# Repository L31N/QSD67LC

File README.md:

View this project on [CADLAB.io](https://cadlab.io/project/1322). 

# QSD67LC
Quickshifter for Triumph Daytona 675 Bj. 06-08

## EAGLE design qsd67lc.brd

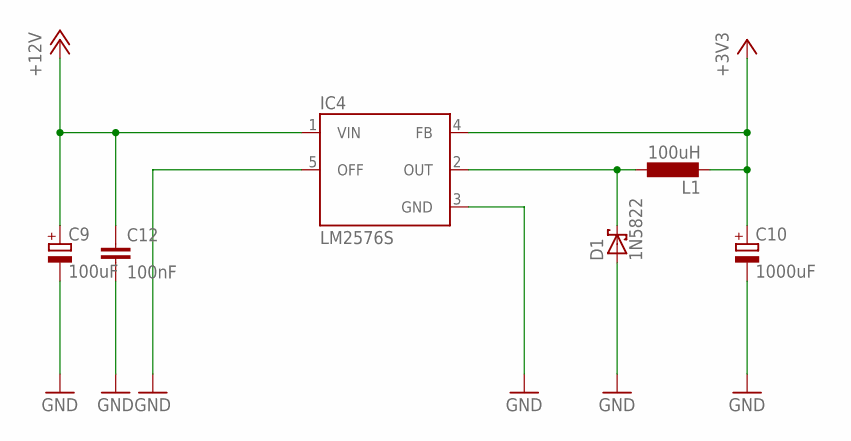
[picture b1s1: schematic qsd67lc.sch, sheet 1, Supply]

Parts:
C9: 100uF; E5-13
C10: 1000uF; E5-10,5
C12: 100nF; C0805
D1: 1N5822; DO201T15
IC4: LM2576S; TO263-5
L1: 100uH; 2200-15.24

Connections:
+3V3: C10.+, IC4.4 (FB), L1.2; also elsewhere on the board
+12V: C9.+, C12.1, IC4.1 (VIN); also elsewhere on the board
GND: C9.-, C10.-, C12.2, D1.A, IC4.3 (GND), IC4.5 (OFF); also elsewhere on the board
unnamed: D1.C, IC4.2 (OUT), L1.1

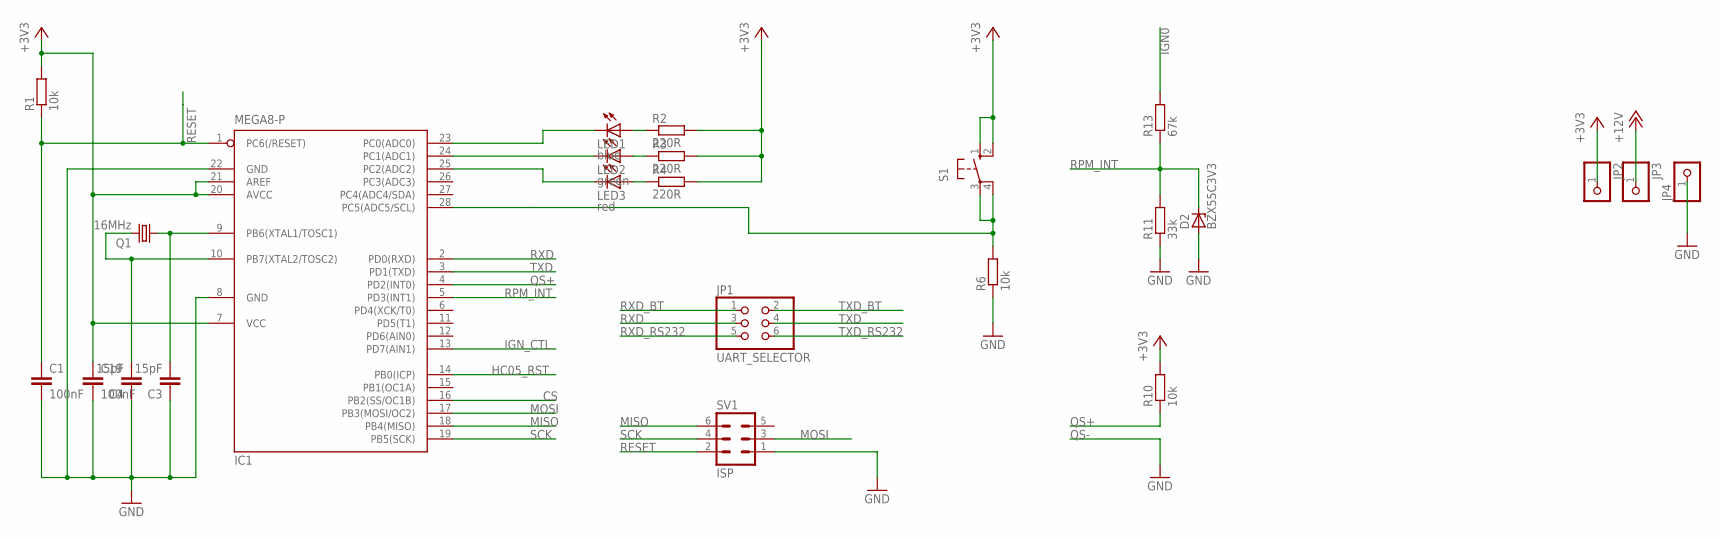
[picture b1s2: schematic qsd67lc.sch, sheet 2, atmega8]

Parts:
C1, C19: 100nF; C0805
C3, C4: 15pF; C0805
D2: BZX55C3V3; DO35Z10
IC1: MEGA8-P; DIL28-3
JP1: UART_SELECTOR; 2X03
JP2, JP3, JP4: PINHD-1X1; 1X01
LED1: blue; CHIP-LED0805
LED2: green; CHIP-LED0805
LED3: red; CHIP-LED0805
Q1: 16MHz; HC18U-V
R1, R6, R10: 10k; R0805
R2, R3, R4: 220R; R0805
R11: 33k; R0805
R13: 67k; R0805
S1: 10-XX; B3F-10XX
SV1: ISP; ML6

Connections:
+3V3: C19.1, IC1.7 (VCC), IC1.20 (AVCC), IC1.21 (AREF), JP2.1, R1.2, R2.2, R3.2, R4.2, R10.2, S1.1 (S), S1.2 (S1); also elsewhere on the board
+12V: JP3.1; also elsewhere on the board
CS: IC1.16 (PB2(SS/OC1B))
GND: C1.2, C3.1, C4.1, C19.2, D2.A, IC1.8 (GND), IC1.22 (GND), JP4.1, R6.1, R11.1, SV1.1; also elsewhere on the board
HC05_RST: IC1.14 (PB0(ICP)); also elsewhere on the board
IGN0: R13.2; also elsewhere on the board
IGN_CTL: IC1.13 (PD7(AIN1)); also elsewhere on the board
MISO: IC1.18 (PB4(MISO)), SV1.6
MOSI: IC1.17 (PB3(MOSI/OC2)), SV1.3
unnamed: IC1.24 (PC1(ADC1)), LED2.C
unnamed: C3.2, IC1.9 (PB6(XTAL1/TOSC1)), Q1.1
unnamed: C4.2, IC1.10 (PB7(XTAL2/TOSC2)), Q1.2
unnamed: LED2.A, R3.1
unnamed: LED1.A, R2.1
unnamed: LED3.A, R4.1
unnamed: IC1.23 (PC0(ADC0)), LED1.C
unnamed: IC1.25 (PC2(ADC2)), LED3.C
unnamed: IC1.28 (PC5(ADC5/SCL)), R6.2, S1.3, S1.4 (P1)
QS+: IC1.4 (PD2(INT0)), R10.1; also elsewhere on the board
RESET: C1.1, IC1.1 (PC6(/RESET)), R1.1, SV1.2
RPM_INT: D2.C, IC1.5 (PD3(INT1)), R11.2, R13.1
RXD: IC1.2 (PD0(RXD)), JP1.3
RXD_BT: JP1.1; also elsewhere on the board
RXD_RS232: JP1.5; also elsewhere on the board
SCK: IC1.19 (PB5(SCK)), SV1.4
TXD: IC1.3 (PD1(TXD)), JP1.4
TXD_BT: JP1.2; also elsewhere on the board
TXD_RS232: JP1.6; also elsewhere on the board

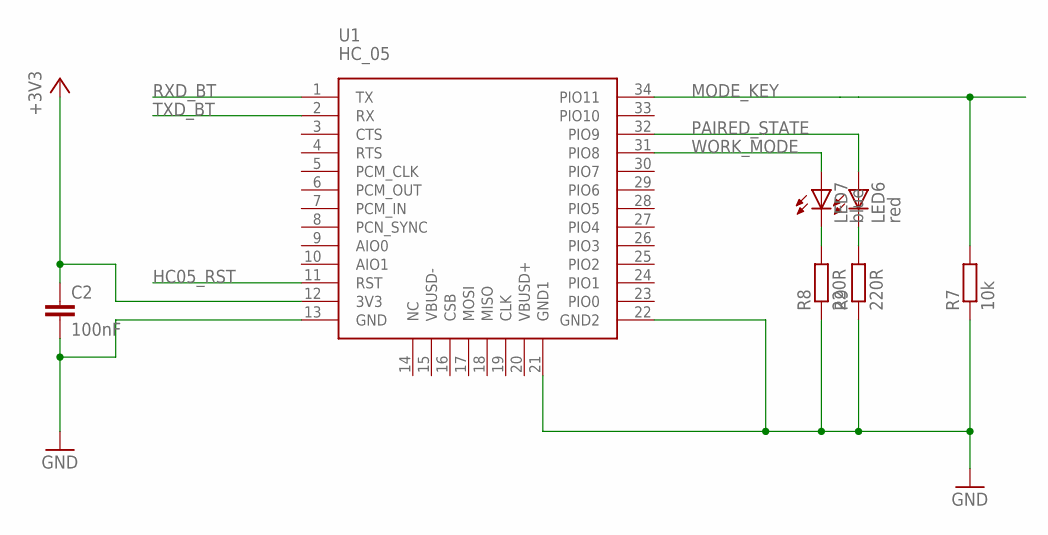
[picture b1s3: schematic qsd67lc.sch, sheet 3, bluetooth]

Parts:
C2: 100nF; C0805
LED6: red; CHIP-LED0805
LED7: blue; CHIP-LED0805
R7: 10k; R0805
R8, R9: 220R; R0805
U1: HC_05; BLUETOOTH_SMD

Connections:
+3V3: C2.1, U1.12 (3V3); also elsewhere on the board
GND: C2.2, R7.1, R8.1, R9.1, U1.13 (GND), U1.21 (GND1), U1.22 (GND2); also elsewhere on the board
HC05_RST: U1.11 (RST); also elsewhere on the board
MODE_KEY: R7.2, U1.34 (PIO11)
unnamed: LED7.C, R8.2
unnamed: LED6.C, R9.2
PAIRED_STATE: LED6.A, U1.32 (PIO9)
RXD_BT: U1.1 (TX); also elsewhere on the board
TXD_BT: U1.2 (RX); also elsewhere on the board
WORK_MODE: LED7.A, U1.31 (PIO8)

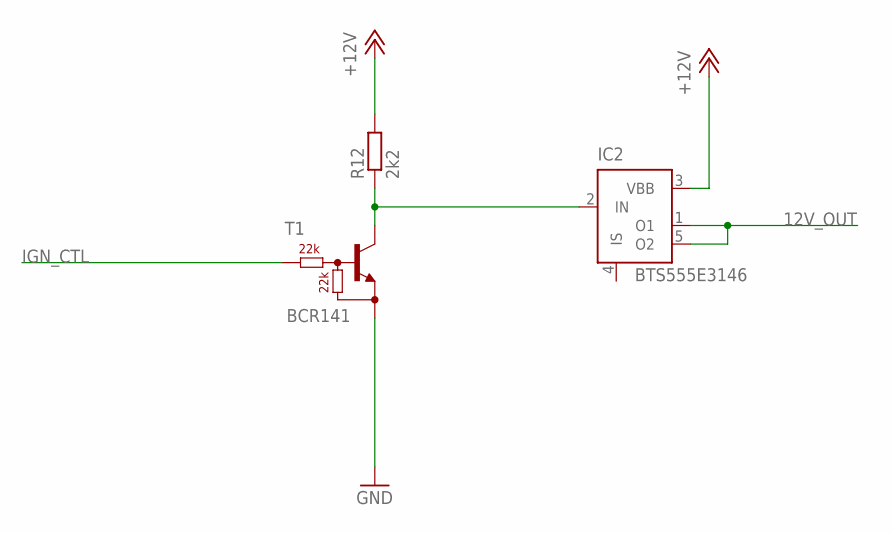
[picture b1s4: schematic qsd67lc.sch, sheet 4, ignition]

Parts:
IC2: BTS555E3146; TO220-52
R12: 2k2; R0805
T1: BCR141; SOT23-R_INFINEON

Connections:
12V_OUT: IC2.1 (O1), IC2.5 (O2); also elsewhere on the board
+12V: IC2.3 (VBB), R12.2; also elsewhere on the board
GND: T1.2 (E); also elsewhere on the board
IGN_CTL: T1.1 (B); also elsewhere on the board
unnamed: IC2.2 (IN), R12.1, T1.3 (C)

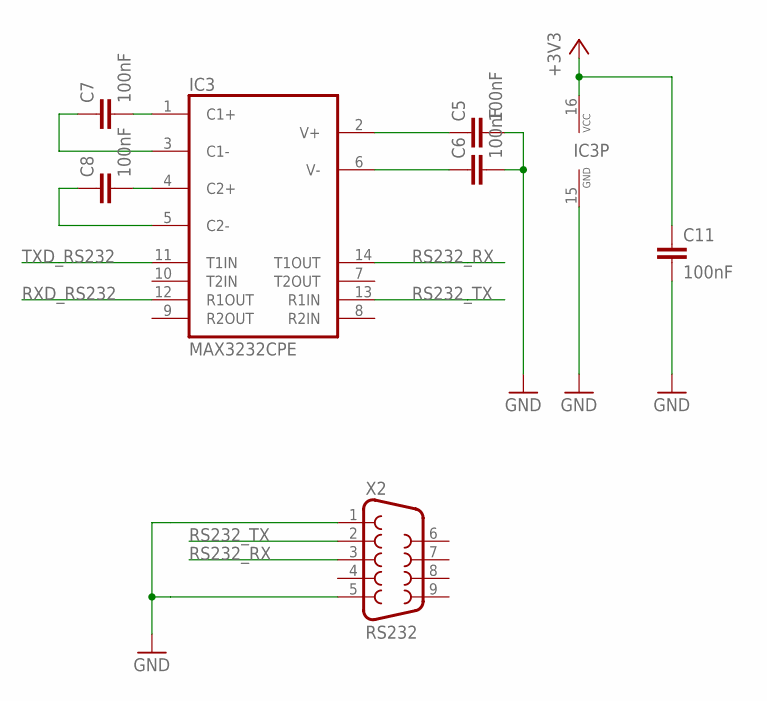
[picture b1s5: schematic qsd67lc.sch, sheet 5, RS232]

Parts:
C5, C6, C7, C8, C11: 100nF; C0805
IC3: MAX3232CPE; DIL16
X2: RS232; F09HP

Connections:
+3V3: C11.1, IC3.16 (VCC); also elsewhere on the board
GND: C5.2, C6.2, C11.2, IC3.15 (GND), X2.1, X2.5; also elsewhere on the board
unnamed: C5.1, IC3.2 (V+)
unnamed: C6.1, IC3.6 (V-)
unnamed: C7.2, IC3.1 (C1+)
unnamed: C8.2, IC3.4 (C2+)
unnamed: C8.1, IC3.5 (C2-)
unnamed: C7.1, IC3.3 (C1-)
RS232_RX: IC3.14 (T1OUT), X2.3
RS232_TX: IC3.13 (R1IN), X2.2
RXD_RS232: IC3.12 (R1OUT); also elsewhere on the board
TXD_RS232: IC3.11 (T1IN); also elsewhere on the board

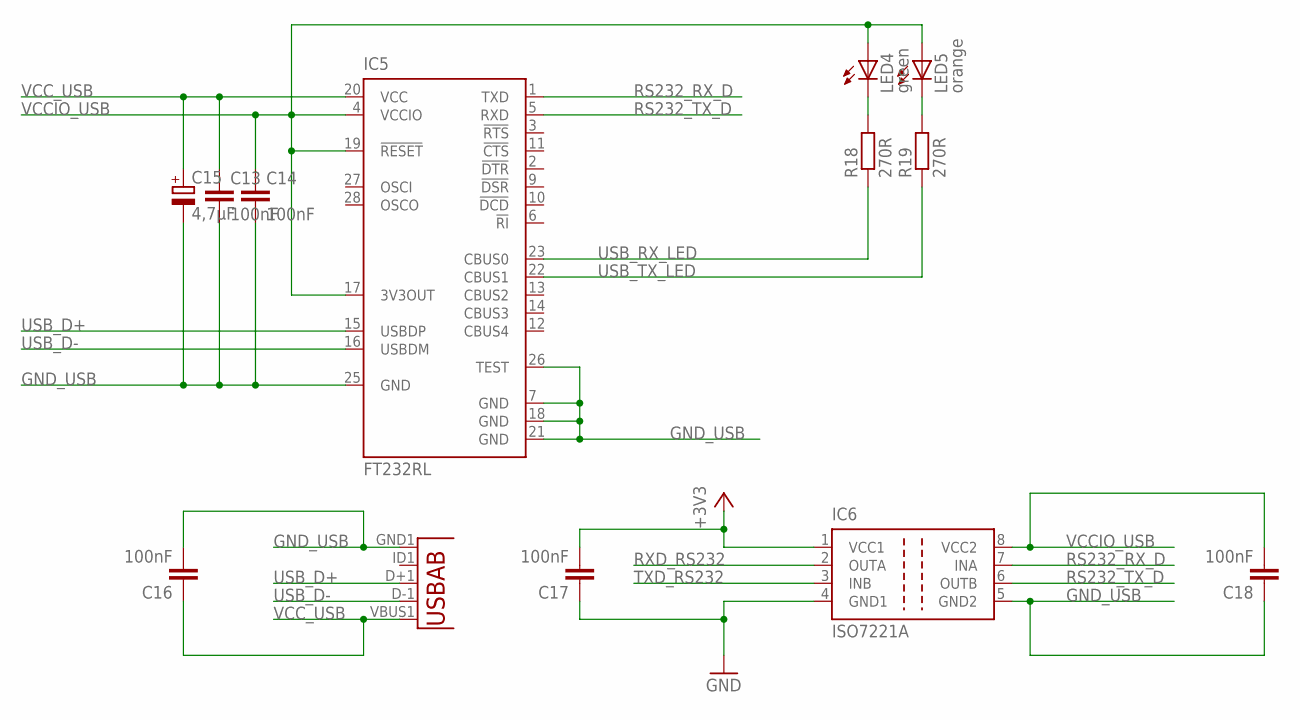
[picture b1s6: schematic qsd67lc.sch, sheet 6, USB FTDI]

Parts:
C13, C14, C16, C17, C18: 100nF; C0805
C15: 4,7µF; E2,5-5
IC5: FT232RL; SSOP28
IC6: ISO7221A; SO-08
LED4: green; SML0805
LED5: orange; SML0805
R18, R19: 270R; R0805
U2: USB""; USB-MICRO-SMD

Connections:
+3V3: C17.2, IC6.1 (VCC1); also elsewhere on the board
GND: C17.1, IC6.4 (GND1); also elsewhere on the board
GND_USB: C13.2, C14.2, C15.-, C16.2, C18.1, IC5.7 (GND), IC5.18 (GND), IC5.21 (GND), IC5.25 (GND), IC5.26 (TEST), IC6.5 (GND2), U2.GND1 (GND)
unnamed: LED4.C, R18.2
unnamed: LED5.C, R19.2
RS232_RX_D: IC5.1 (TXD), IC6.7 (INA)
RS232_TX_D: IC5.5 (RXD), IC6.6 (OUTB)
RXD_RS232: IC6.2 (OUTA); also elsewhere on the board
TXD_RS232: IC6.3 (INB); also elsewhere on the board
USB_D+: IC5.15 (USBDP), U2.D+1 (D+)
USB_D-: IC5.16 (USBDM), U2.D-1 (D-)
USB_RX_LED: IC5.23 (CBUS0), R18.1
USB_TX_LED: IC5.22 (CBUS1), R19.1
VCCIO_USB: C14.1, C18.2, IC5.4 (VCCIO), IC5.17 (3V3OUT), IC5.19 (!RESET), IC6.8 (VCC2), LED4.A, LED5.A
VCC_USB: C13.1, C15.+, C16.1, IC5.20 (VCC), U2.VBUS1 (VBUS)

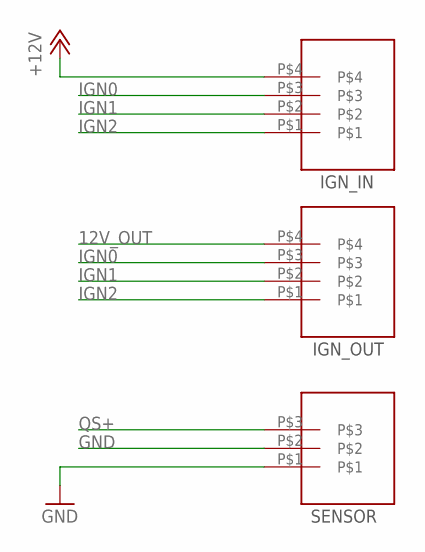
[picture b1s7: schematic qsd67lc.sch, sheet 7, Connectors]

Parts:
CON1, CON2: RIA-AKL-230-04; CON-RIA-P4
CON3: RIA-AKL-230-03; CON-RIA-P3

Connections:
12V_OUT: CON2.P$4; also elsewhere on the board
+12V: CON1.P$4; also elsewhere on the board
GND: CON3.P$1, CON3.P$2; also elsewhere on the board
IGN0: CON1.P$3, CON2.P$3; also elsewhere on the board
IGN1: CON1.P$2, CON2.P$2
IGN2: CON1.P$1, CON2.P$1
QS+: CON3.P$3; also elsewhere on the board

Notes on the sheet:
IGN_IN
IGN_OUT
SENSOR

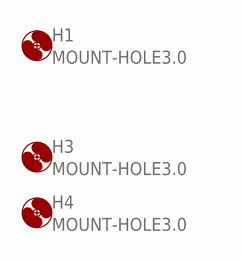
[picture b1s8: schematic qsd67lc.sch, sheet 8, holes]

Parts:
H1, H3, H4: MOUNT-HOLE3.0; 3,0

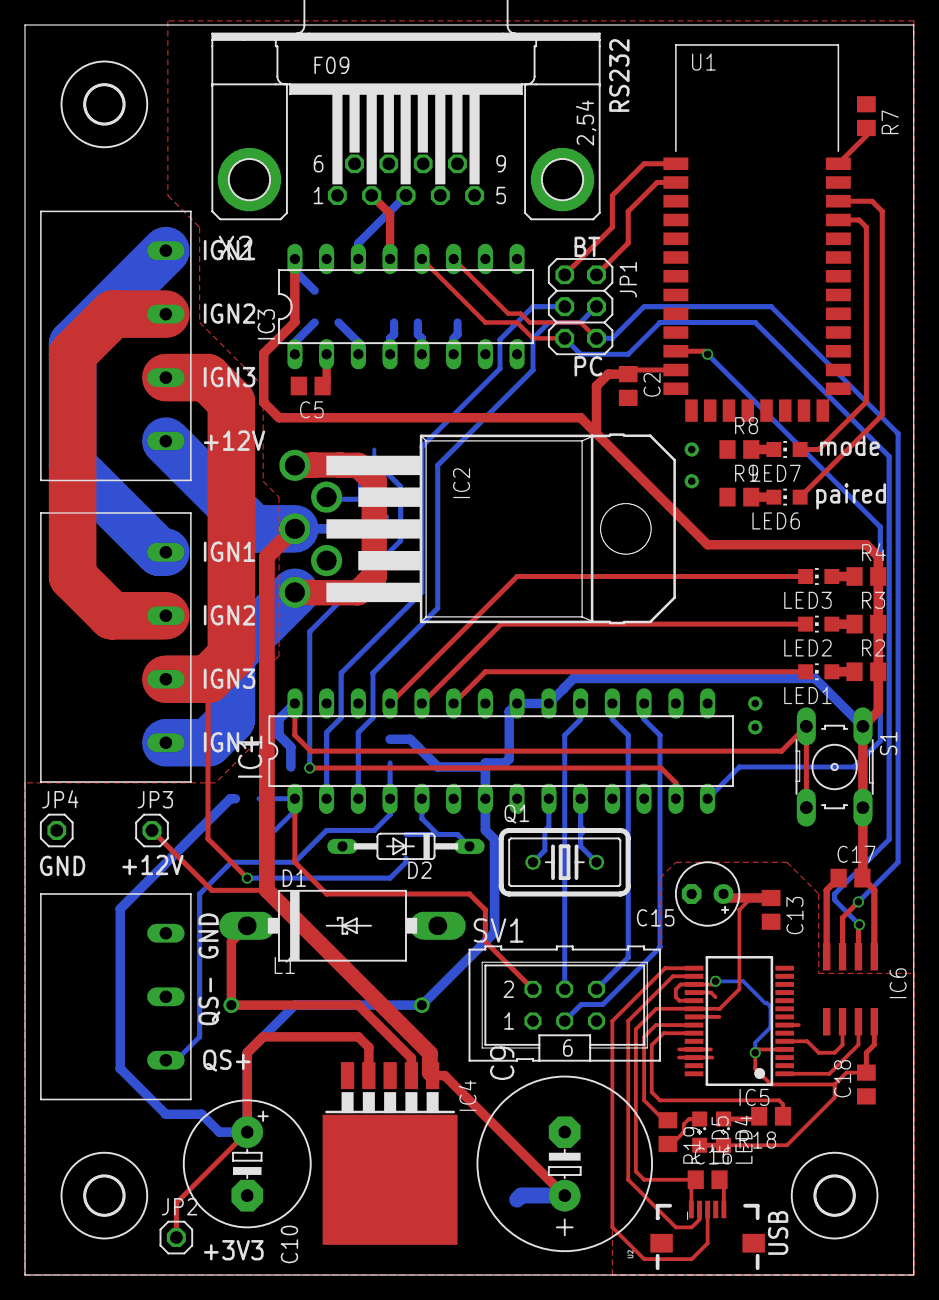
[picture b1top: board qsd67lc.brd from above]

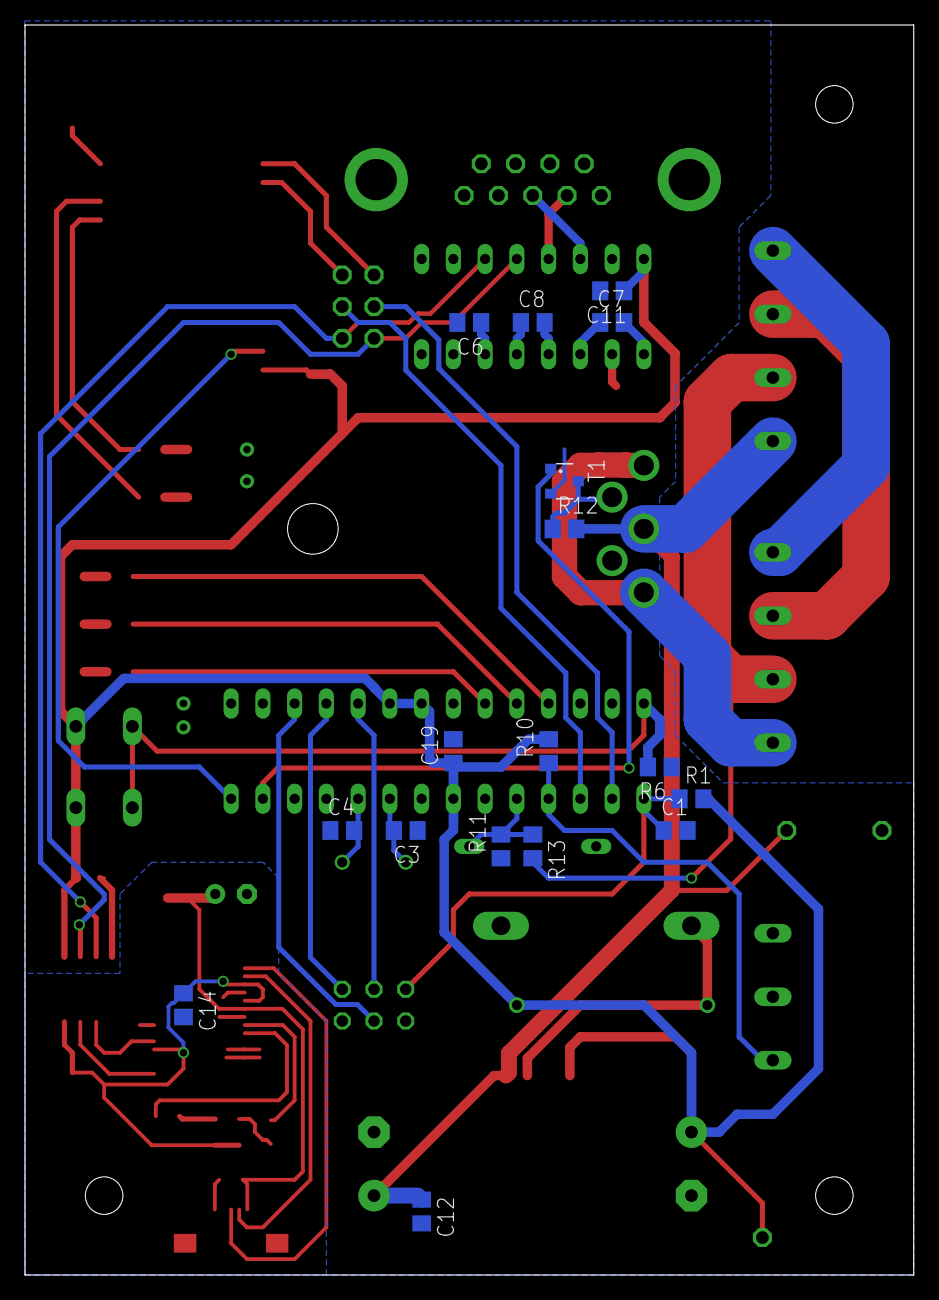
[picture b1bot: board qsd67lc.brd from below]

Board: 2 copper layers, 71.1 x 100.0 mm, 66 parts (17 on the bottom side), 56 nets.

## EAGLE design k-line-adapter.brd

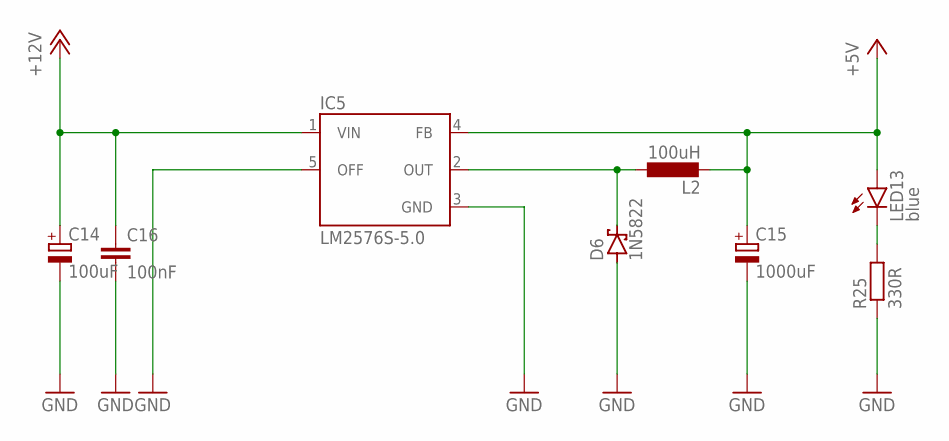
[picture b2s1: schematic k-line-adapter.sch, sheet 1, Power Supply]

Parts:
C14: 100uF; E5-10,5
C15: 1000uF; E5-10,5
C16: 100nF; C0805
D6: 1N5822; DO201T15
IC5: LM2576S-5.0; TO263-5
L2: 100uH; 09HCP
LED13: blue; CHIP-LED0805
R25: 330R; R0805

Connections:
+5V: C15.+, IC5.4 (FB), L2.P$2 (2), LED13.A; also elsewhere on the board
+12V: C14.+, C16.1, IC5.1 (VIN); also elsewhere on the board
GND: C14.-, C15.-, C16.2, D6.A, IC5.3 (GND), IC5.5 (OFF), R25.1; also elsewhere on the board
unnamed: D6.C, IC5.2 (OUT), L2.P$1 (1)
unnamed: LED13.C, R25.2

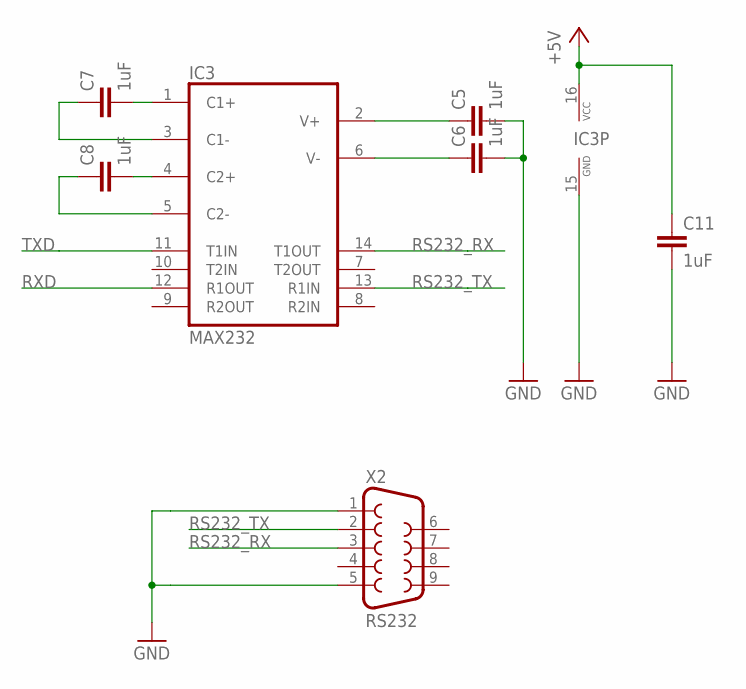
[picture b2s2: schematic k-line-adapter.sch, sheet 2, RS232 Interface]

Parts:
C5, C6, C7, C8, C11: 1uF; C0805
IC3: MAX232; DIL16
X2: RS232; F09HP

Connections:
+5V: C11.1, IC3.16 (VCC); also elsewhere on the board
GND: C5.2, C6.2, C11.2, IC3.15 (GND), X2.1, X2.5; also elsewhere on the board
unnamed: C5.1, IC3.2 (V+)
unnamed: C6.1, IC3.6 (V-)
unnamed: C7.2, IC3.1 (C1+)
unnamed: C8.2, IC3.4 (C2+)
unnamed: C8.1, IC3.5 (C2-)
unnamed: C7.1, IC3.3 (C1-)
RS232_RX: IC3.14 (T1OUT), X2.3
RS232_TX: IC3.13 (R1IN), X2.2
RXD: IC3.12 (R1OUT); also elsewhere on the board
TXD: IC3.11 (T1IN); also elsewhere on the board

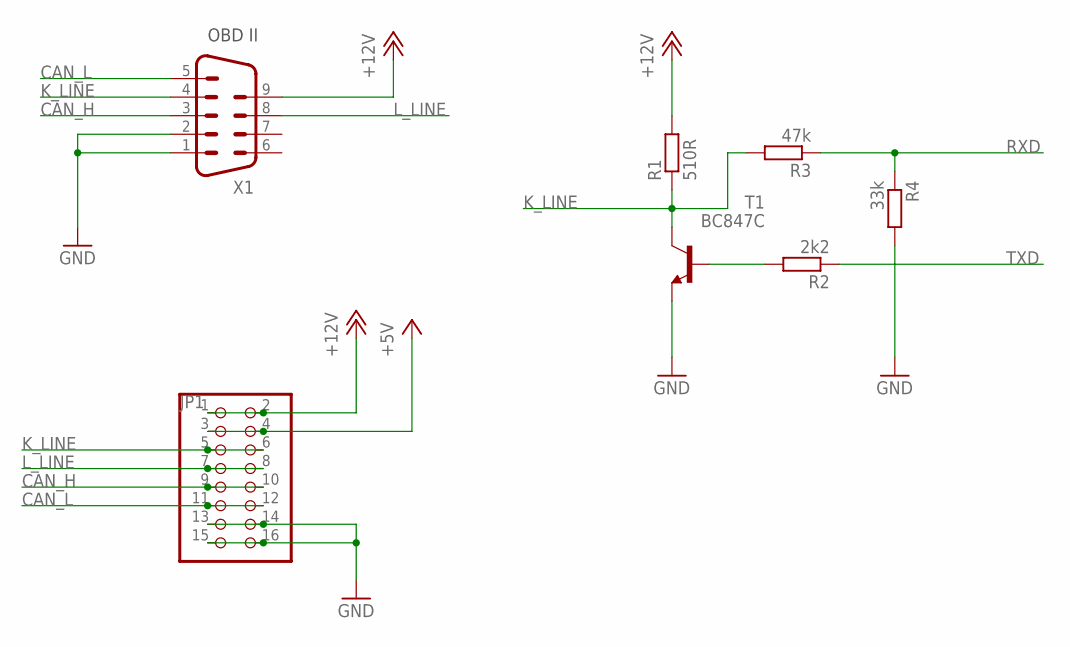
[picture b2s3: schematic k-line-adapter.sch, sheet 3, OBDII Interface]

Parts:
JP1: PINHD-2X8; 2X08
R1: 510R; R0805
R2: 2k2; R0805
R3: 47k; R0805
R4: 33k; R0805
T1: BC847C; SOT23-BEC
X1: M09HP

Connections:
+5V: JP1.3, JP1.4; also elsewhere on the board
+12V: JP1.1, JP1.2, R1.2, X1.9; also elsewhere on the board
CAN_H: JP1.9, JP1.10, X1.3
CAN_L: JP1.11, JP1.12, X1.5
GND: JP1.13, JP1.14, JP1.15, JP1.16, R4.2, T1.E, X1.1, X1.2; also elsewhere on the board
K_LINE: JP1.5, JP1.6, R1.1, R3.2, T1.C, X1.4
L_LINE: JP1.7, JP1.8, X1.8
unnamed: R2.2, T1.B
RXD: R3.1, R4.1; also elsewhere on the board
TXD: R2.1; also elsewhere on the board

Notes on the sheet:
OBD II

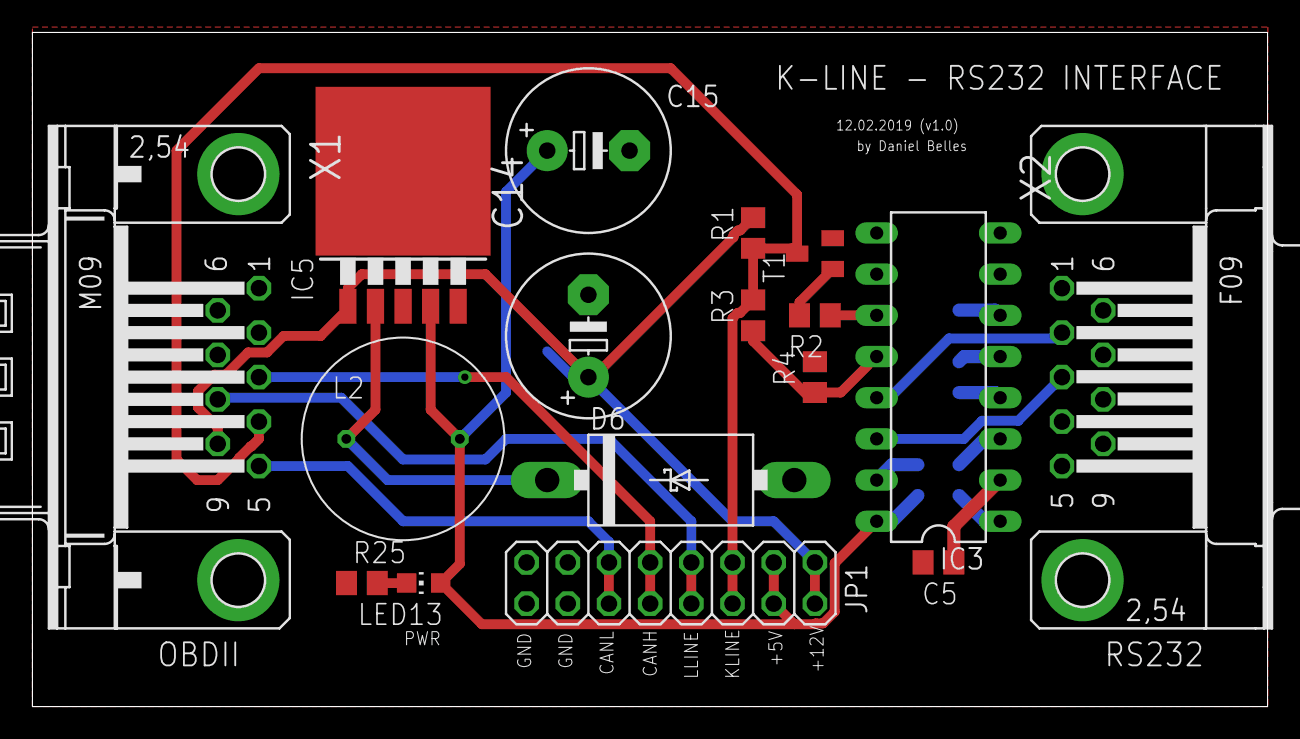
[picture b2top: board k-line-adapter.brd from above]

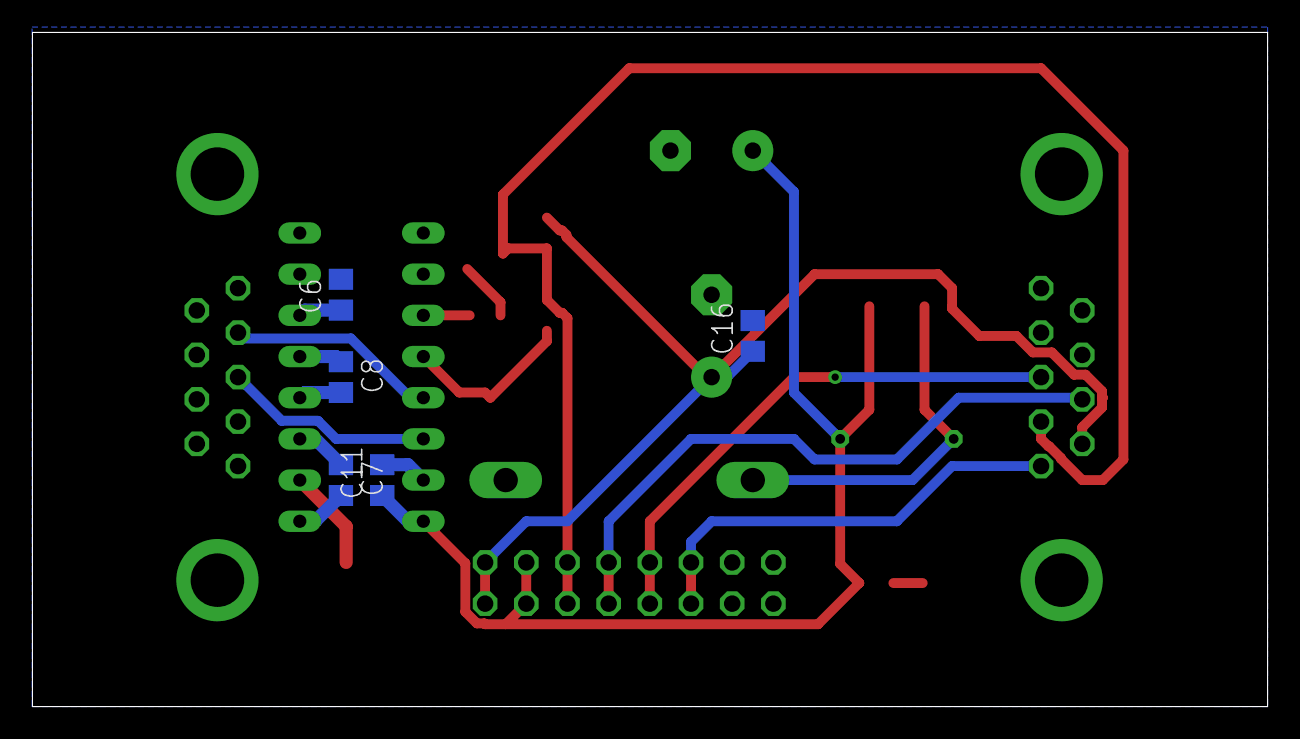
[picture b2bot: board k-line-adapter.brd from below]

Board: 2 copper layers, 76.2 x 41.6 mm, 22 parts (5 on the bottom side), 20 nets.

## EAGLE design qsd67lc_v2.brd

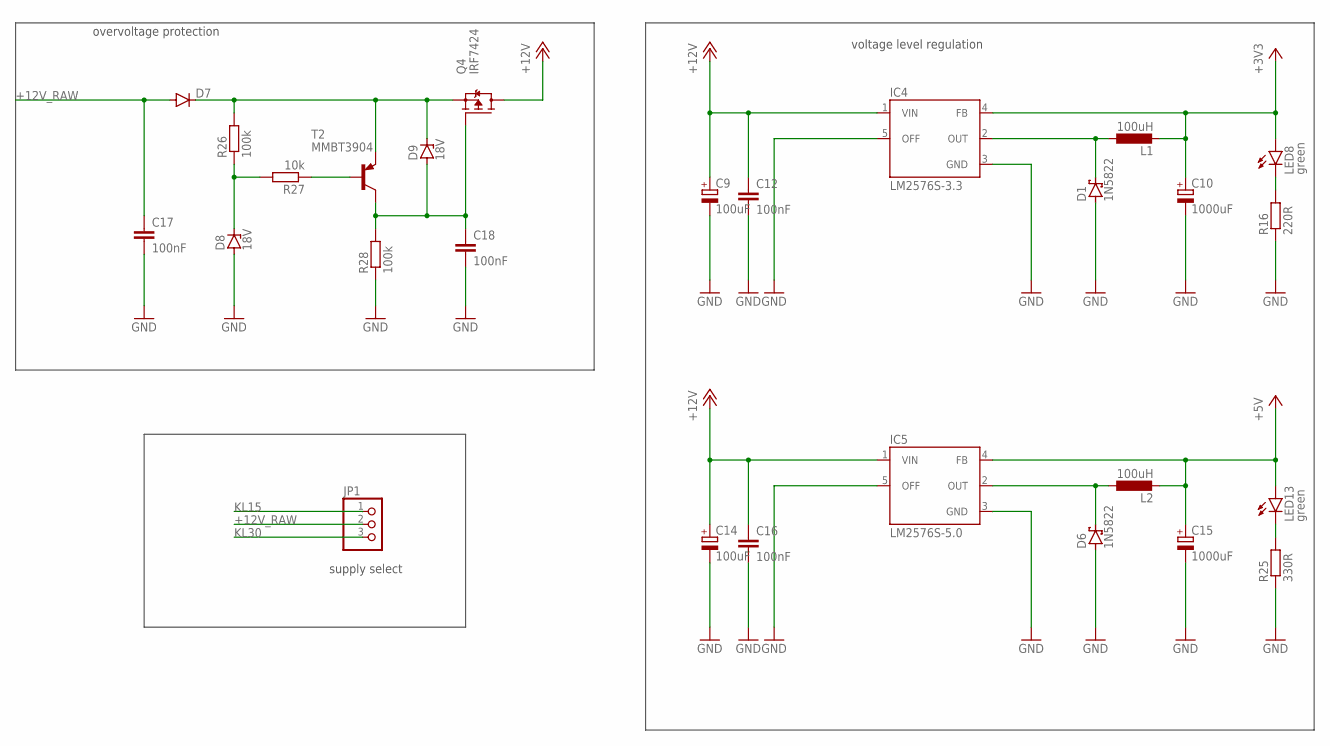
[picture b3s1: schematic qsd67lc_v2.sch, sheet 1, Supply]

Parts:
C9, C14: 100uF; E5-10,5
C10, C15: 1000uF; E5-10,5
C12, C16, C17, C18: 100nF; C0805
D1, D6: 1N5822; DO201T15
D7: DIODE-SOD123; SOD123
D8, D9: 18V; SOD80C
IC4: LM2576S-3.3; TO263-5
IC5: LM2576S-5.0; TO263-5
JP1: PINHD-1X3; 1X03
L1, L2: 100uH; 09HCP
LED8, LED13: green; CHIP-LED0805
Q4: IRF7424; SO-8
R16: 220R; R0805
R25: 330R; R0805
R26, R28: 100k; R0805
R27: 10k; R0805
T2: MMBT3904; SOT23-BEC

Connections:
+3V3: C10.+, IC4.4 (FB), L1.P$2 (2), LED8.A; also elsewhere on the board
+5V: C15.+, IC5.4 (FB), L2.P$2 (2), LED13.A; also elsewhere on the board
+12V: C9.+, C12.1, C14.+, C16.1, IC4.1 (VIN), IC5.1 (VIN), Q4.5 (D), Q4.6 (D), Q4.7 (D), Q4.8 (D); also elsewhere on the board
+12V_RAW: C17.1, D7.A, JP1.2
GND: C9.-, C10.-, C12.2, C14.-, C15.-, C16.2, C17.2, C18.2, D1.A, D6.A, D8.A, IC4.3 (GND), IC4.5 (OFF), IC5.3 (GND), IC5.5 (OFF), R16.1, R25.1, R28.1; also elsewhere on the board
KL15: JP1.1; also elsewhere on the board
KL30: JP1.3; also elsewhere on the board
unnamed: LED8.C, R16.2
unnamed: D7.C, D9.C, Q4.1 (S), Q4.2 (S), Q4.3 (S), R26.2, T2.E
unnamed: D1.C, IC4.2 (OUT), L1.P$1 (1)
unnamed: D6.C, IC5.2 (OUT), L2.P$1 (1)
unnamed: LED13.C, R25.2
unnamed: D8.C, R26.1, R27.2
unnamed: R27.1, T2.B
unnamed: C18.1, D9.A, Q4.4 (G), R28.2, T2.C

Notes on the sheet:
supply select
overvoltage protection
voltage level regulation

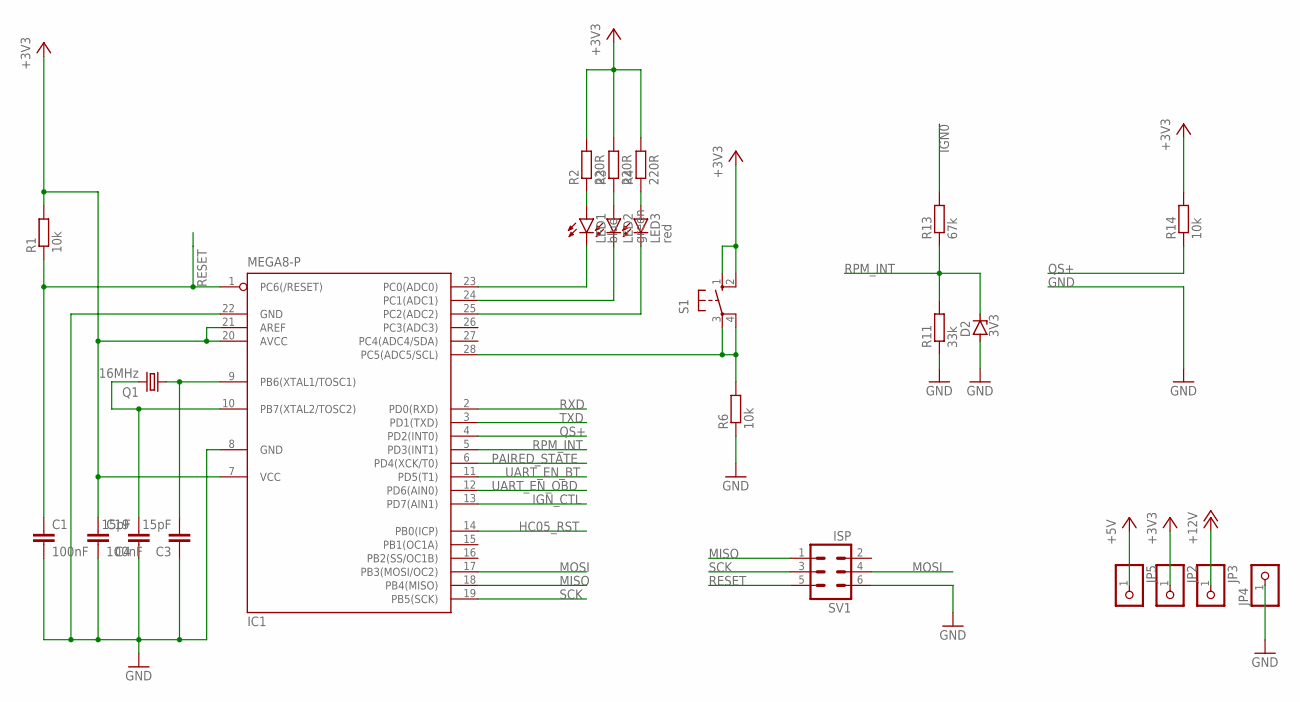
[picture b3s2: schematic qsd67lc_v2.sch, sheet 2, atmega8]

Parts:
C1, C19: 100nF; C0805
C3, C4: 15pF; C0805
D2: 3V3; SOD80C
IC1: MEGA8-P; DIL28-3
JP2, JP3, JP4, JP5: PINHD-1X1; 1X01
LED1: blue; CHIP-LED0805
LED2: green; CHIP-LED0805
LED3: red; CHIP-LED0805
Q1: 16MHz; HC49U-V
R1, R6, R14: 10k; R0805
R2, R3, R4: 220R; R0805
R11: 33k; R0805
R13: 67k; R0805
S1: 10-XX; B3F-10XX
SV1: ISP; ML6

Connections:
+3V3: C19.1, IC1.7 (VCC), IC1.20 (AVCC), IC1.21 (AREF), JP2.1, R1.2, R2.2, R3.2, R4.2, R14.2, S1.1 (S), S1.2 (S1); also elsewhere on the board
+5V: JP5.1; also elsewhere on the board
+12V: JP3.1; also elsewhere on the board
GND: C1.2, C3.1, C4.1, C19.2, D2.A, IC1.8 (GND), IC1.22 (GND), JP4.1, R6.1, R11.1, SV1.6; also elsewhere on the board
HC05_RST: IC1.14 (PB0(ICP)); also elsewhere on the board
IGN0: R13.2; also elsewhere on the board
IGN_CTL: IC1.13 (PD7(AIN1)); also elsewhere on the board
MISO: IC1.18 (PB4(MISO)), SV1.1
MOSI: IC1.17 (PB3(MOSI/OC2)), SV1.4
unnamed: C3.2, IC1.9 (PB6(XTAL1/TOSC1)), Q1.1
unnamed: C4.2, IC1.10 (PB7(XTAL2/TOSC2)), Q1.2
unnamed: LED2.A, R3.1
unnamed: LED1.A, R2.1
unnamed: LED3.A, R4.1
unnamed: IC1.23 (PC0(ADC0)), LED1.C
unnamed: IC1.24 (PC1(ADC1)), LED2.C
unnamed: IC1.28 (PC5(ADC5/SCL)), R6.2, S1.3, S1.4 (P1)
unnamed: IC1.25 (PC2(ADC2)), LED3.C
PAIRED_STATE: IC1.6 (PD4(XCK/T0)); also elsewhere on the board
QS+: IC1.4 (PD2(INT0)), R14.1; also elsewhere on the board
RESET: C1.1, IC1.1 (PC6(/RESET)), R1.1, SV1.5
RPM_INT: D2.C, IC1.5 (PD3(INT1)), R11.2, R13.1
RXD: IC1.2 (PD0(RXD)); also elsewhere on the board
SCK: IC1.19 (PB5(SCK)), SV1.3
TXD: IC1.3 (PD1(TXD)); also elsewhere on the board
UART_EN_BT: IC1.11 (PD5(T1)); also elsewhere on the board
UART_EN_OBD: IC1.12 (PD6(AIN0)); also elsewhere on the board

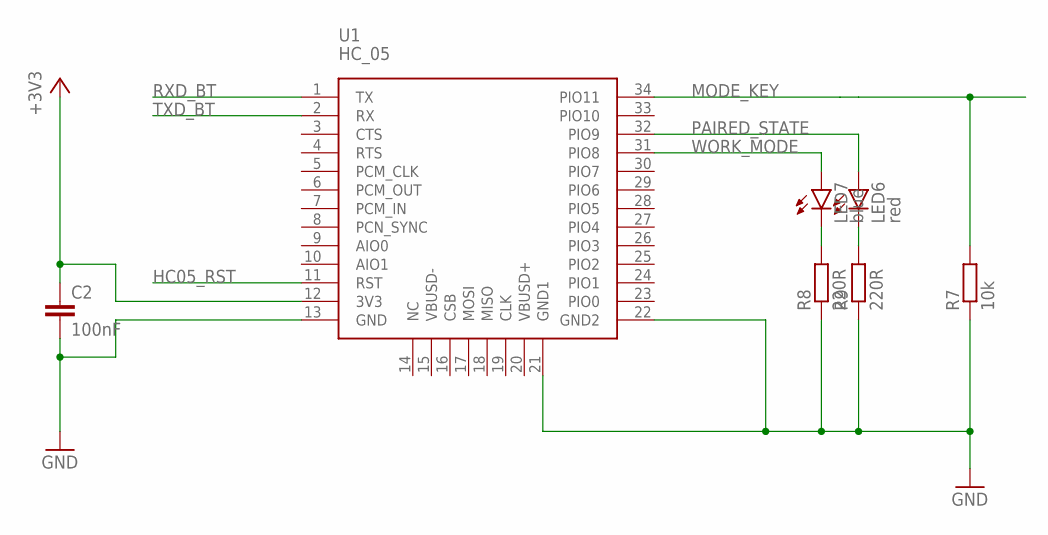
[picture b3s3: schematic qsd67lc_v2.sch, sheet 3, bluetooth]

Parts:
C2: 100nF; C0805
LED6: red; CHIP-LED0805
LED7: blue; CHIP-LED0805
R7: 10k; R0805
R8, R9: 220R; R0805
U1: HC_05; BLUETOOTH_SMD

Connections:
+3V3: C2.1, U1.12 (3V3); also elsewhere on the board
GND: C2.2, R7.1, R8.1, R9.1, U1.13 (GND), U1.21 (GND1), U1.22 (GND2); also elsewhere on the board
HC05_RST: U1.11 (RST); also elsewhere on the board
MODE_KEY: R7.2, U1.34 (PIO11)
unnamed: LED7.C, R8.2
unnamed: LED6.C, R9.2
PAIRED_STATE: LED6.A, U1.32 (PIO9); also elsewhere on the board
RXD_BT: U1.1 (TX); also elsewhere on the board
TXD_BT: U1.2 (RX); also elsewhere on the board
WORK_MODE: LED7.A, U1.31 (PIO8)

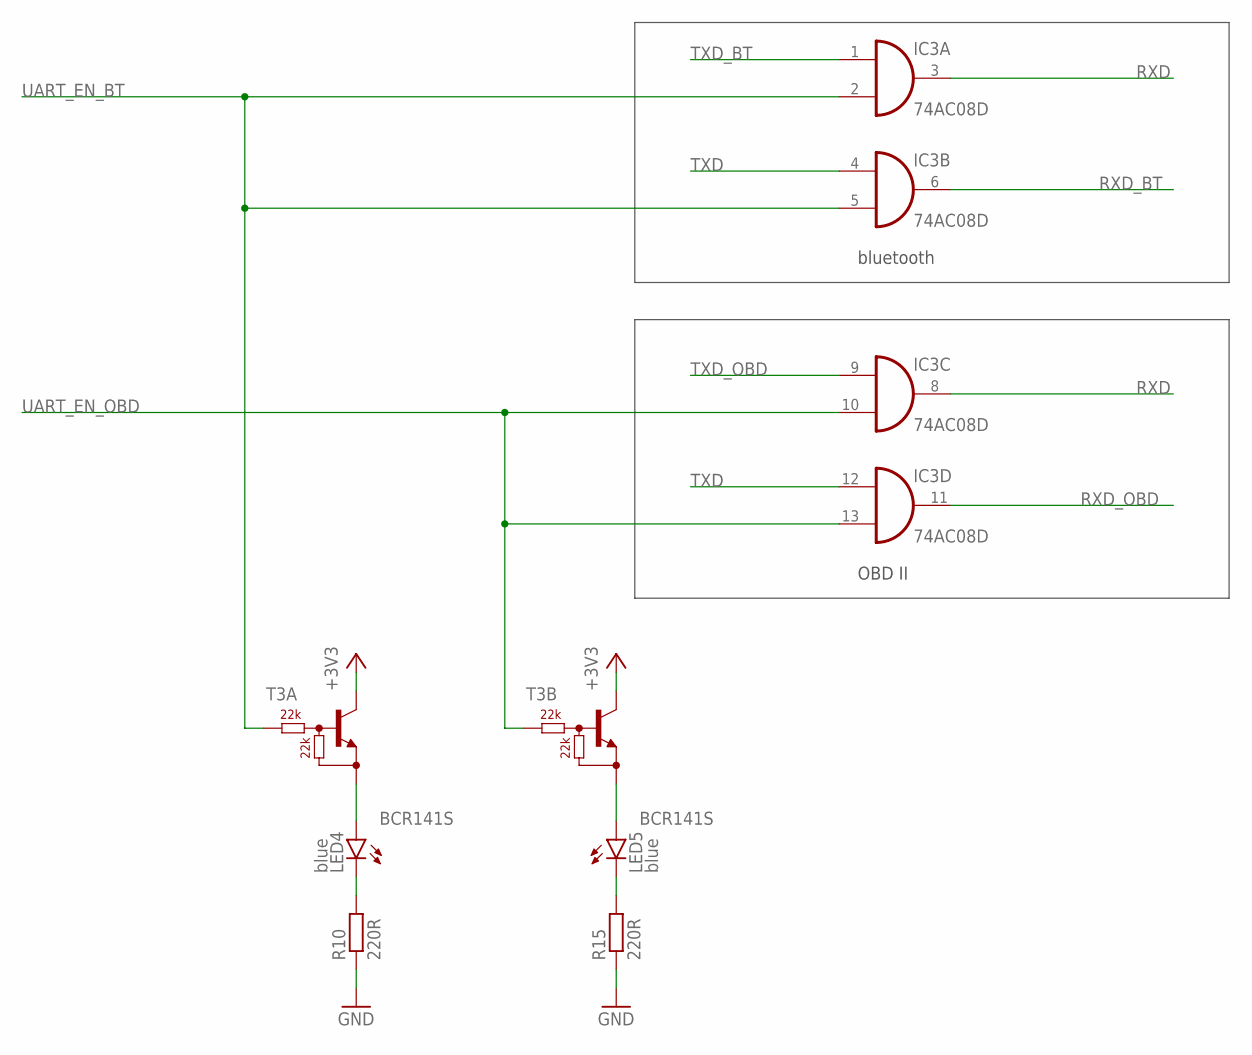
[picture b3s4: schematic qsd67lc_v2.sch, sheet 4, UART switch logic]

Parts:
IC3: 74AC08D; SO14
LED4, LED5: blue; CHIP-LED0805
R10, R15: 220R; M0805
T3: BCR141S; SOT363_INFINEON

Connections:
+3V3: T3.3 (C), T3.6 (C); also elsewhere on the board
GND: IC3.7 (GND), R10.1, R15.1; also elsewhere on the board
unnamed: LED4.C, R10.2
unnamed: LED5.C, R15.2
unnamed: LED4.A, T3.1 (E)
unnamed: LED5.A, T3.4 (E)
RXD: IC3.3 (O), IC3.8 (O); also elsewhere on the board
RXD_BT: IC3.6 (O); also elsewhere on the board
RXD_OBD: IC3.11 (O); also elsewhere on the board
TXD: IC3.4 (I0), IC3.12 (I0); also elsewhere on the board
TXD_BT: IC3.1 (I0); also elsewhere on the board
TXD_OBD: IC3.9 (I0); also elsewhere on the board
UART_EN_BT: IC3.2 (I1), IC3.5 (I1), T3.2 (B); also elsewhere on the board
UART_EN_OBD: IC3.10 (I1), IC3.13 (I1), T3.5 (B); also elsewhere on the board
VCC: IC3.14 (VCC)

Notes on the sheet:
bluetooth
OBD II

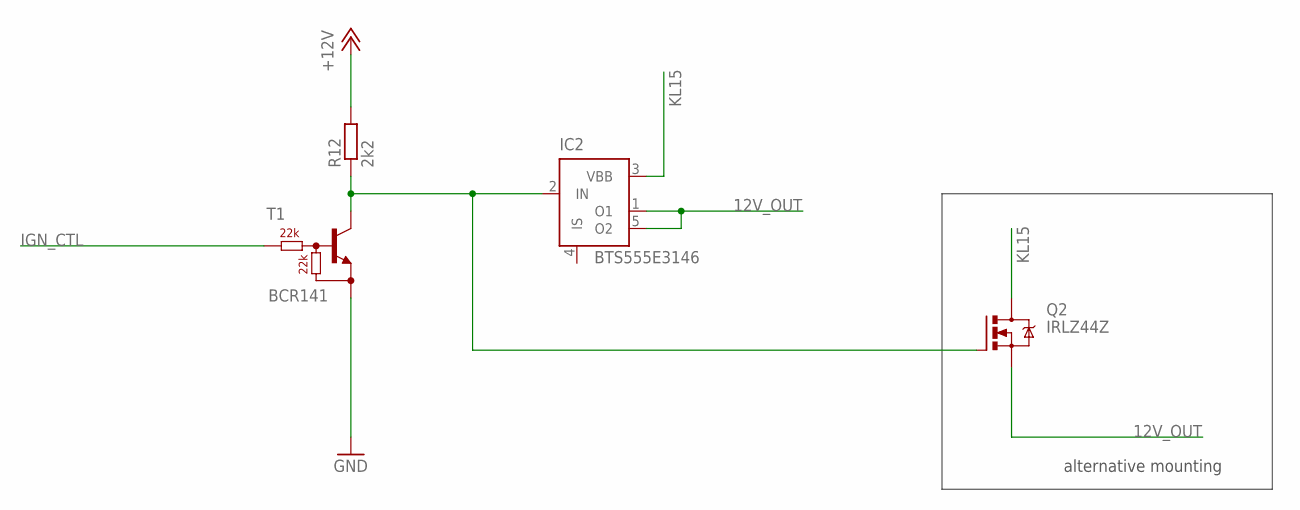
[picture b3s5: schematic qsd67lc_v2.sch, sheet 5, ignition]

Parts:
IC2: BTS555E3146; TO220-52
Q2: IRLZ44Z; TO220BH
R12: 2k2; R0805
T1: BCR141; SOT23-R_INFINEON

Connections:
12V_OUT: IC2.1 (O1), IC2.5 (O2), Q2.S; also elsewhere on the board
+12V: R12.2; also elsewhere on the board
GND: T1.2 (E); also elsewhere on the board
IGN_CTL: T1.1 (B); also elsewhere on the board
KL15: IC2.3 (VBB), Q2.D; also elsewhere on the board
unnamed: IC2.2 (IN), Q2.G, R12.1, T1.3 (C)

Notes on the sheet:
alternative mounting

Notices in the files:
parts and their libraries:
SparkFun-Aesthetics: Licensing: CC v3.0 Share-Alike You are welcome to use this library for commercial purposes.
